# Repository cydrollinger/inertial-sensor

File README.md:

<a href="https://elec-real.com/case-studies/9-axis-inertial-data-logger/"></img></a>

>Electronic Realization L.L.C.								   
>Design: 9 axis inertial sensor with bluetooth communication		   
>Engineer: Cy Drollinger								   
>Date: 2/19												           
>Email: cy@elec-real.com
>Website: https://elec-real.com								   
>Address: 2023 Stadium Dr Suite 2B #210 Bozeman, MT 59715				   
>Phone: 406-539-8117	

**NOTE:**
 This design has been tested and functions as specified. The design is provided gratis, so, please 
 think critically while utilizing and or redesigning. Open electronic circuitry can be dangerous due 
 to easily shorting circuits which can generate immediate and intense heat resulting in fire. Conversation is
 welcome to improve this design and repository, but, be advised ER is a professional design house and
 monetary compensation is required for additional work toward this design enabling your success.			   

**PURPOSE:**
This electronic system is capable of sampling inertial data from the mpu9250 at 1 kHz and storing to 
a uSD card for GB storage, fatfs. The design files were created with Eagle Cadsoft v7.7 as a 
two layer board. Free Eagle version would be capable of viewing, and editing these files for redesign. 

>**File Arcitecture with a terse description**

* FOLDERS:
	* docs		: datasheets charging IC and battery holder
	* hardware	: eagle cadsoft(v7.7) hardware design files 	
		* eagleup		: 3D files 
		* library		: eagle part files 
		* manufacturing	: files required to produce the design
			* bom	: files created to order the parts
					* batteryCharger.txt	: 
					* batteryv1.1.csv	: digikey order
					* hundredUnits.txt	
			* gerber	: files generated to manufacture the board
			* <a href="https://oshpark.com/shared_projects/Yydb06ED"></img></a>
	* firmware
	* software

	* readme.md	: this file

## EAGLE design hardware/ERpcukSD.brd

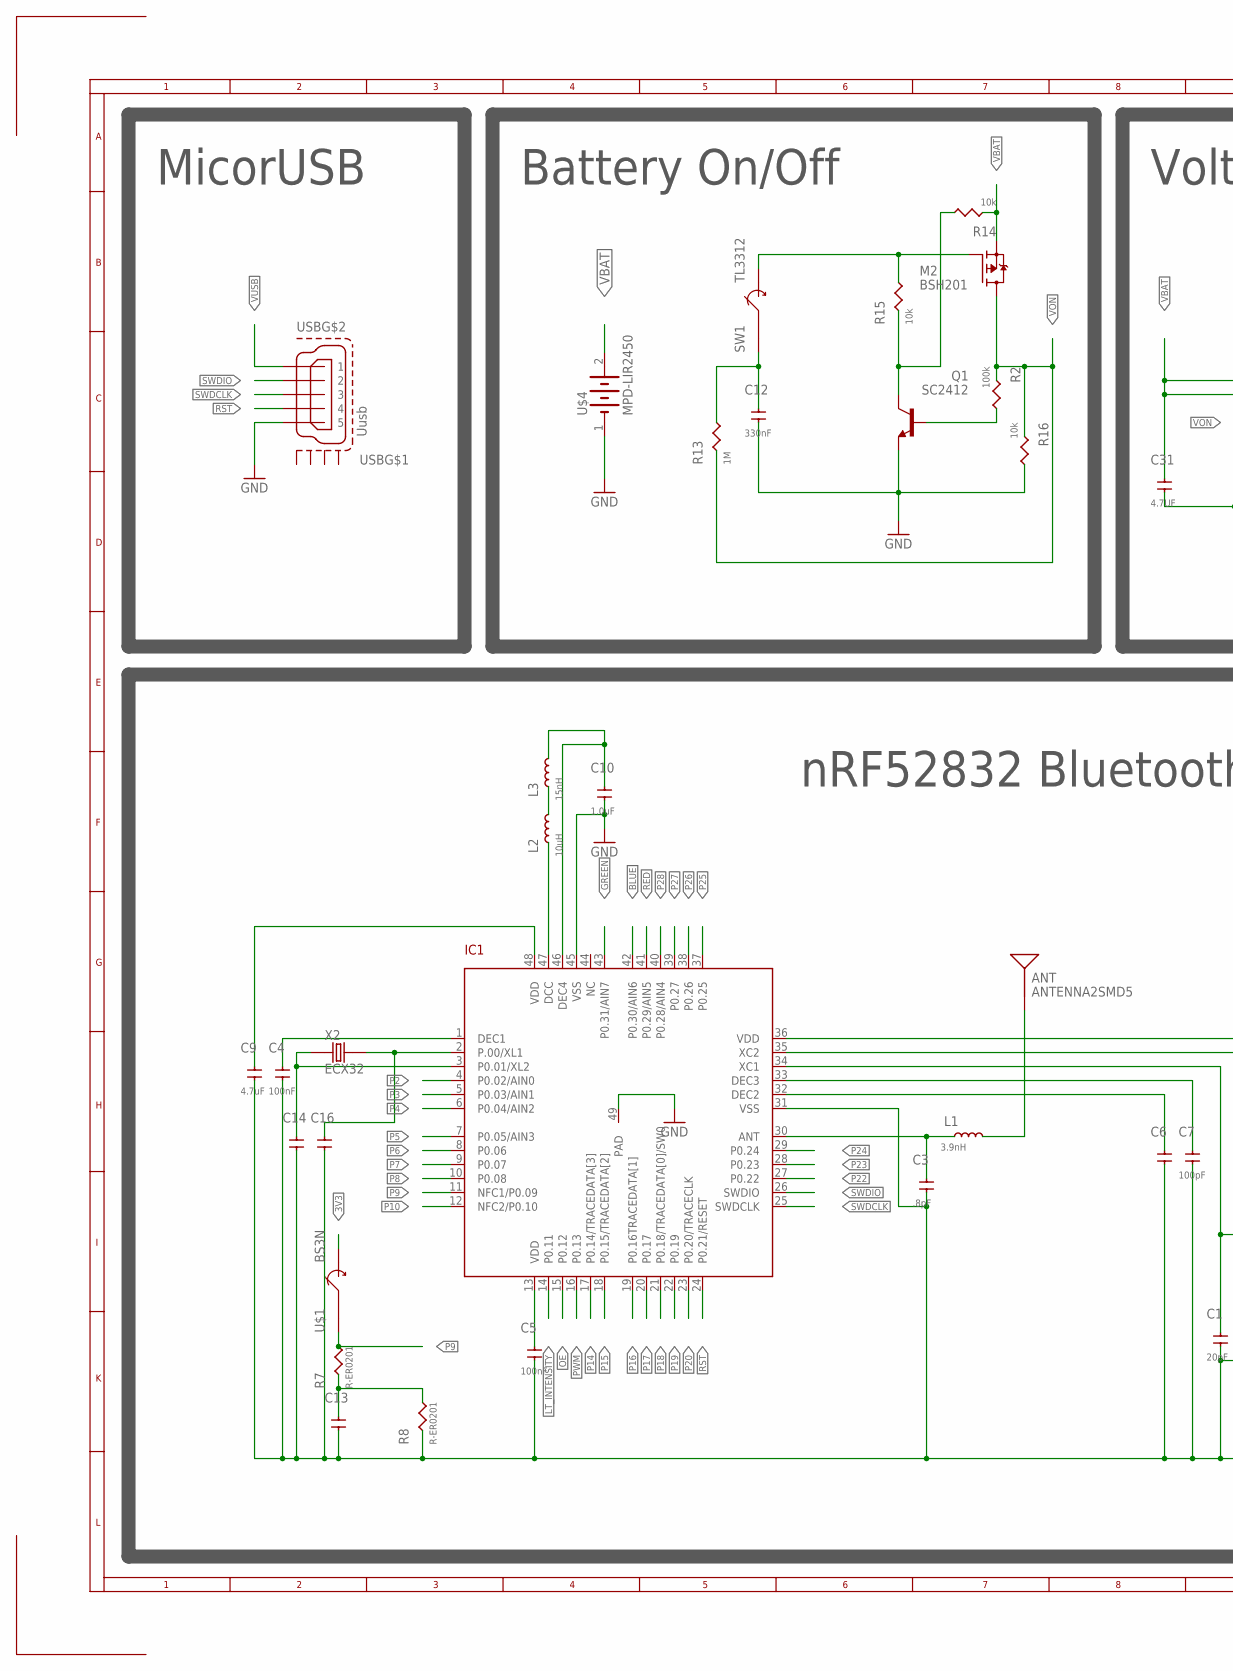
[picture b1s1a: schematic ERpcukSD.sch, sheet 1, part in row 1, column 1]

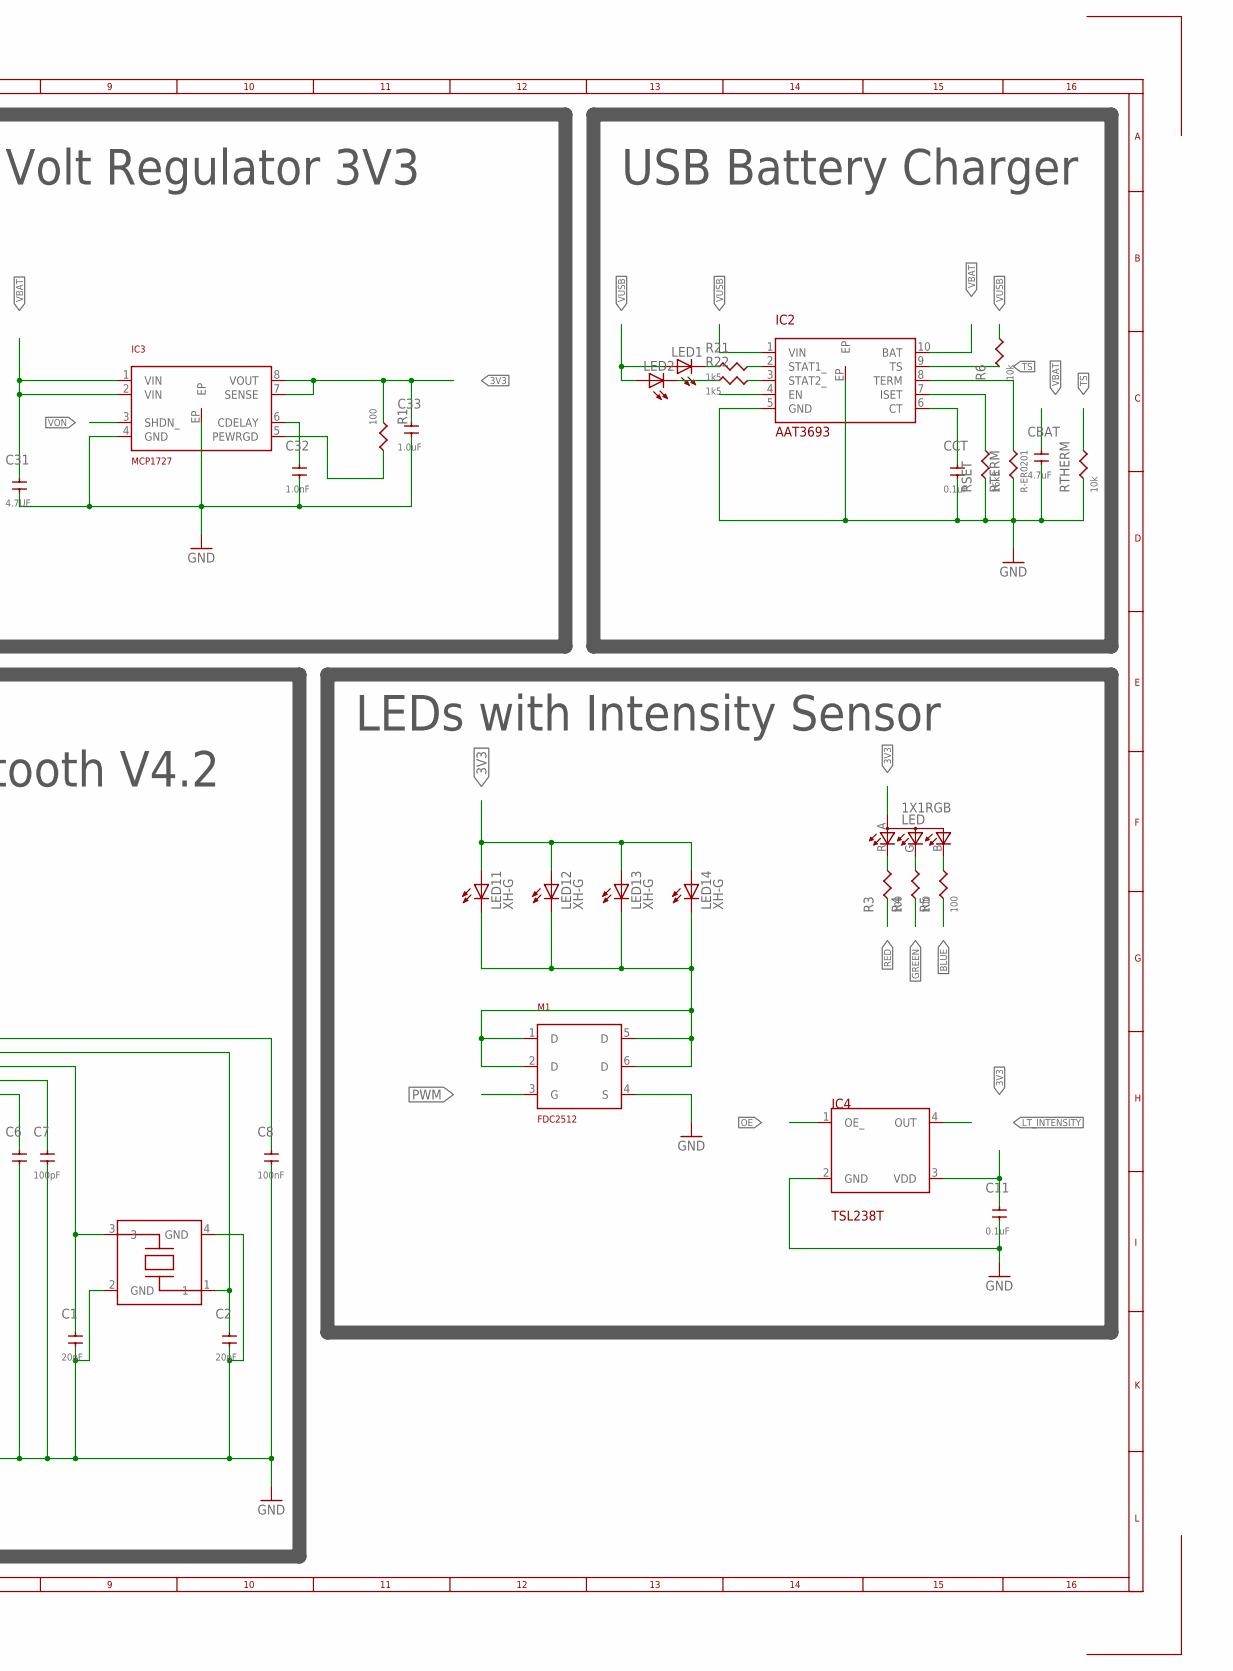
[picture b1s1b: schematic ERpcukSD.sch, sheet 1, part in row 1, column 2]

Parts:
ANT: ANTENNA2SMD5; ANTENNA-CHIP5
C1, C2: 20pF; C0201
C3: .8pF; C0201
C4, C5, C8: 100nF; C0201
C6, C13, C14, C16: C-ER201; C0201
C7: 100pF; C0201
C9: 4.7uF; C0402
C10, C33: 1.0uF; C0201
C11: 0.1uF; C0201
C12: 330nF; C0201
C31: 4.7UF; C0402
C32: 1.0nF; C0201
CBAT: 4.7uF; C0402
CCT: 0.1uF; C0201
IC1: NRF52832; QFN48
IC2: AAT3693
IC3: MCP1727; DFN8-3X3
IC4: TSL238T; T4
L1: 3.9nH; C0201
L2: 10uH; R0603
L3: 15nH; C0201
LED: 1X1RGB; 1X1
LED1, LED2: LEDCHIP-LED0603; CHIP-LED0603
LED11, LED12, LED13, LED14: XH-G
M1: FDC2512; SSOT6
M2: BSH201; SOT23
Q1: SC2412; SC59-BEC
R1, R3, R4, R5: 100; R0201
R2: 100k; R0201
R6, R14, R15, R16: 10k; R0201
R7, R8: R-ER0201; R0201
R13: 1M; R0201
R21, R22: 1k5; R0201
RSET: 16k5; R0201
RTERM: R-ER0201; R0201
RTHERM: 10k; R0201
SW1: TL3312; DIGIKEY EG4620CT-ND
U$1: BS3N
U$4: MPD-LIR2450; LIR2450
USB: Uusb; ZX62R-B-5P
X1: FA-128
X2: ECX32; ECX39

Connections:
3V3: C5.2, C8.2, C9.2, C11.2, C33.2, IC1.13 (VDD), IC1.36 (VDD), IC1.48 (VDD), IC3.7 (SENSE), IC3.8 (VOUT), IC4.3 (VDD), LED.A (A2), LED11.2 (A), LED12.2 (A), LED13.2 (A), LED14.2 (A), R1.1, U$1.2; also elsewhere on the board
BLUE: IC1.42 (P0.30/AIN6), R5.1
GND: C1.1, C2.1, C3.1, C4.1, C5.1, C6.1, C7.1, C8.1, C9.1, C10.1, C11.1, C12.1, C13.1, C14.1, C16.1, C31.1, C32.1, C33.1, CBAT.1, CCT.1, IC1.31 (VSS), IC1.45 (VSS), IC1.49 (PAD), IC2.5 (GND), IC2.EP, IC3.4 (GND), IC3.EP, IC4.2 (GND), M1.4 (S), Q1.E, R8.1, R16.2, RSET.1, RTERM.1, RTHERM.1, U$4.1 (-), USB.1 (5), X1.2 (GND), X1.4 (GND); also elsewhere on the board
GREEN: IC1.43 (P0.31/AIN7), R4.1
LT_INTENSITY: IC1.14 (P0.11), IC4.4 (OUT)
unnamed: LED11.1 (C), LED12.1 (C), LED13.1 (C), LED14.1 (C), M1.1 (D), M1.2 (D), M1.5 (D), M1.6 (D)
unnamed: Q1.B, R2.2
unnamed: C3.2, IC1.30 (ANT), L1.1
unnamed: C6.2, IC1.32 (DEC2)
unnamed: ANT.FEED, L1.2
unnamed: C7.2, IC1.33 (DEC3)
unnamed: C1.2, IC1.34 (XC1), X1.3
unnamed: C2.2, IC1.35 (XC2), X1.1
unnamed: Q1.C, R14.2, R15.1
unnamed: IC1.47 (DCC), L2.1
unnamed: L2.2, L3.1
unnamed: C10.2, IC1.46 (DEC4), L3.2
unnamed: C12.2, R13.2, SW1.1
unnamed: LED.B (CGREEN), R5.2
unnamed: CCT.2, IC2.6 (CT)
unnamed: IC2.7 (ISET), RSET.2
unnamed: IC2.8 (TERM), RTERM.2
unnamed: IC2.3 (STAT2_), R22.2
unnamed: IC2.2 (STAT1_), R21.2
unnamed: LED1.C, R21.1
unnamed: LED2.C, R22.1
unnamed: LED.G (CBLUE), R4.2
unnamed: IC3.5 (PEWRGD), R1.2
unnamed: LED.R (CRED), R3.2
unnamed: C32.2, IC3.6 (CDELAY)
unnamed: M2.1 (G), R15.2, SW1.3 (2)
unnamed: C16.2, IC1.2 (P.00/XL1), X2.P$2 (2)
unnamed: C14.2, IC1.3 (P0.01/XL2), X2.P$1 (1)
unnamed: C4.2, IC1.1 (DEC1)
unnamed: C13.2, R7.1, R8.2
OE: IC1.15 (P0.12), IC4.1 (OE_)
P2: IC1.4 (P0.02/AIN0); also elsewhere on the board
P3: IC1.5 (P0.03/AIN1); also elsewhere on the board
P4: IC1.6 (P0.04/AIN2); also elsewhere on the board
P5: IC1.7 (P0.05/AIN3); also elsewhere on the board
P6: IC1.8 (P0.06); also elsewhere on the board
P7: IC1.9 (P0.07); also elsewhere on the board
P8: IC1.10 (P0.08); also elsewhere on the board
P9: IC1.11 (NFC1/P0.09), R7.2, U$1.1
P10: IC1.12 (NFC2/P0.10); also elsewhere on the board
P14: IC1.17 (P0.14/TRACEDATA[3]); also elsewhere on the board
P15: IC1.18 (P0.15/TRACEDATA[2]); also elsewhere on the board
P16: IC1.19 (P0.16TRACEDATA[1]); also elsewhere on the board
P17: IC1.20 (P0.17); also elsewhere on the board
P18: IC1.21 (P0.18/TRACEDATA[0]/SW0); also elsewhere on the board
P19: IC1.22 (P0.19); also elsewhere on the board
P20: IC1.23 (P0.20/TRACECLK); also elsewhere on the board
P22: IC1.27 (P0.22); also elsewhere on the board
P23: IC1.28 (P0.23)
P24: IC1.29 (P0.24)
P25: IC1.37 (P0.25)
P26: IC1.38 (P0.26)
P27: IC1.39 (P0.27)
P28: IC1.40 (P0.28/AIN4)
PWM: IC1.16 (P0.13), M1.3 (G)
RED: IC1.41 (P0.29/AIN5), R3.1
RST: IC1.24 (P0.21/RESET), USB.2 (4)
SWDCLK: IC1.25 (SWDCLK), USB.3
SWDIO: IC1.26 (SWDIO), USB.4 (2)
TS: IC2.9 (TS), R6.1, RTHERM.2
VBAT: C31.2, CBAT.2, IC2.10 (BAT), IC3.1 (VIN), IC3.2 (VIN), M2.2 (S), R14.1, U$4.2 (+)
VON: IC3.3 (SHDN_), M2.3 (D), R2.1, R13.1, R16.1
VUSB: IC2.1 (VIN), IC2.4 (EN), LED1.A, LED2.A, R6.2, USB.5 (1)

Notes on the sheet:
nRF52832 Bluetooth V4.2
MicorUSB
Battery On/Off
Volt Regulator 3V3
USB Battery Charger
LEDs with Intensity Sensor

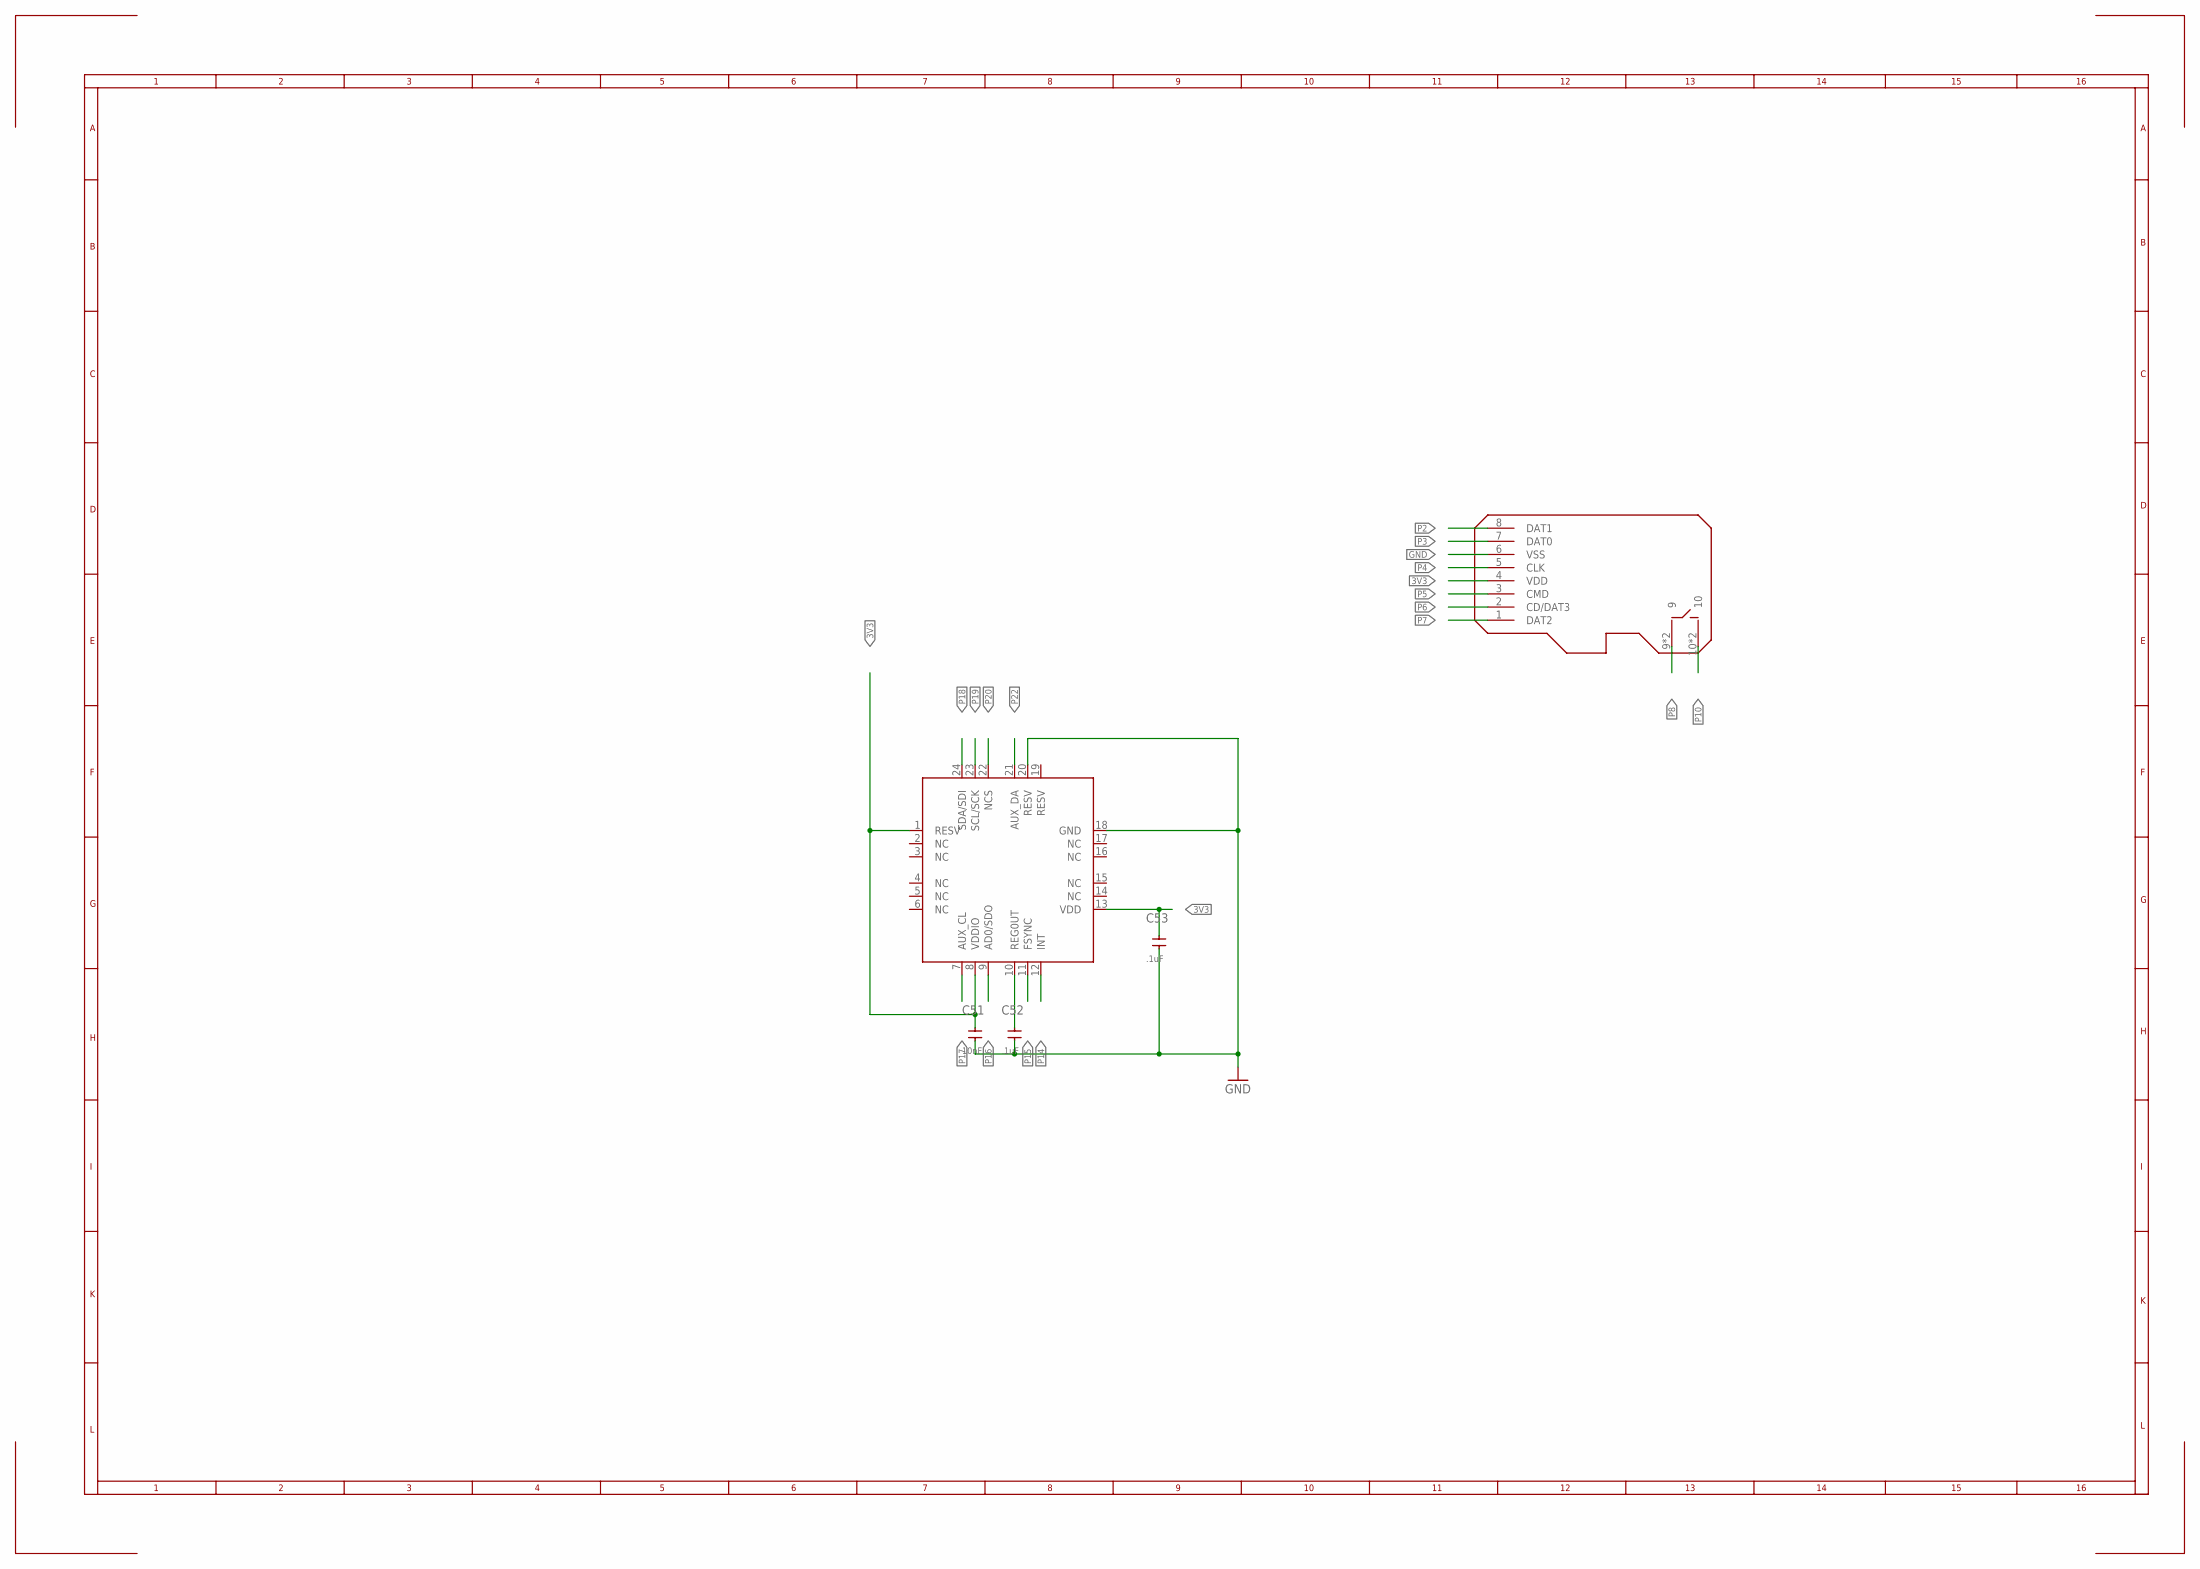
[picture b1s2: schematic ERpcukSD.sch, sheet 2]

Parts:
C51: 10nF; C0201
C52, C53: .1uF; C0201
IC5: MPU9250; 3X3_24_QFN_CORRECTED
U$2: MICROSD

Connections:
3V3: C51.2, C53.2, IC5.1 (RESV), IC5.8 (VDDIO), IC5.13 (VDD), U$2.4 (VDD); also elsewhere on the board
GND: C51.1, C52.1, C53.1, IC5.18 (GND), IC5.20 (RESV), U$2.6 (VSS); also elsewhere on the board
unnamed: C52.2, IC5.10 (REG0UT)
P2: U$2.8 (DAT1); also elsewhere on the board
P3: U$2.7 (DAT0); also elsewhere on the board
P4: U$2.5 (CLK); also elsewhere on the board
P5: U$2.3 (CMD); also elsewhere on the board
P6: U$2.2 (CD/DAT3); also elsewhere on the board
P7: U$2.1 (DAT2); also elsewhere on the board
P8: U$2.9, U$2.9@1 (9); also elsewhere on the board
P10: U$2.10, U$2.10@1 (10); also elsewhere on the board
P14: IC5.12 (INT); also elsewhere on the board
P15: IC5.11 (FSYNC); also elsewhere on the board
P16: IC5.9 (AD0/SDO); also elsewhere on the board
P17: IC5.7 (AUX_CL); also elsewhere on the board
P18: IC5.24 (SDA/SDI); also elsewhere on the board
P19: IC5.23 (SCL/SCK); also elsewhere on the board
P20: IC5.22 (NCS); also elsewhere on the board
P22: IC5.21 (AUX_DA); also elsewhere on the board

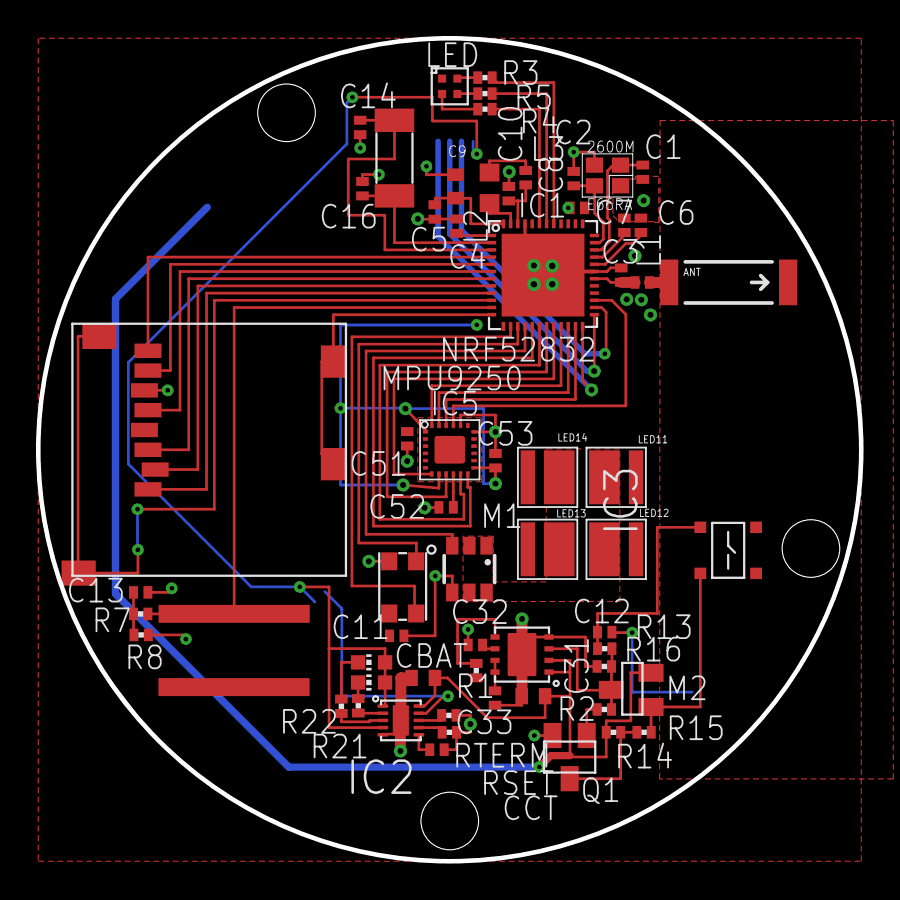
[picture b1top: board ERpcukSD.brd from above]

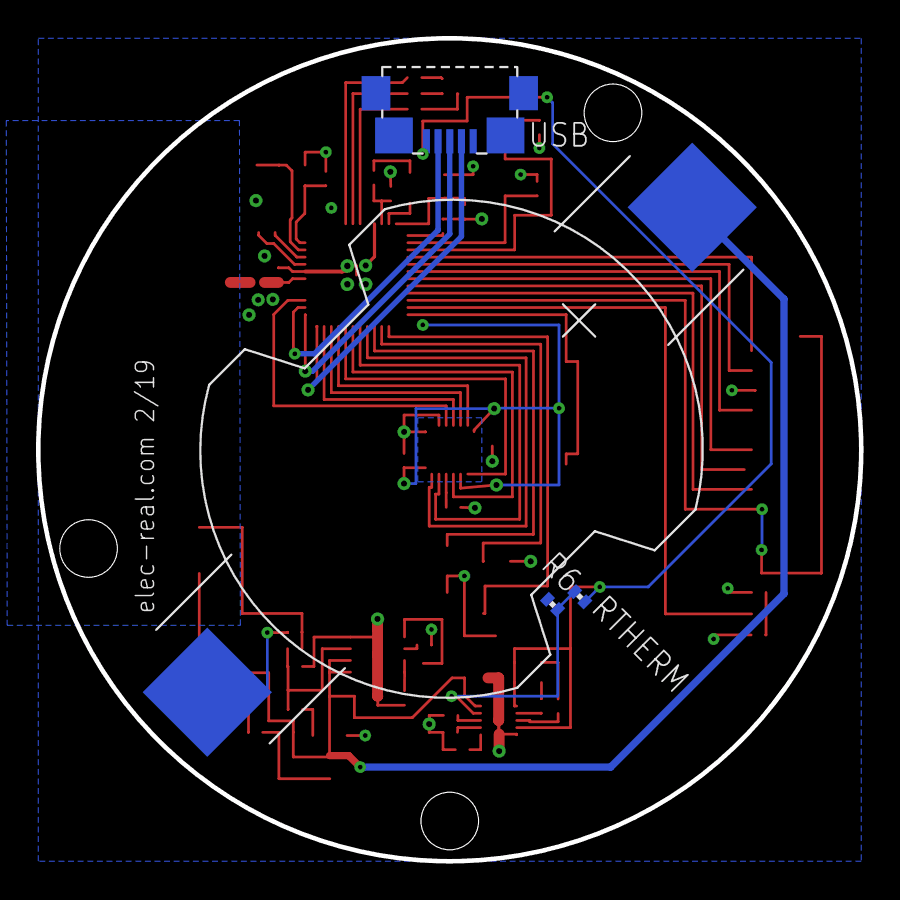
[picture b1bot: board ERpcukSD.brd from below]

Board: 2 copper layers, 45.7 x 45.7 mm, 66 parts (4 on the bottom side), 63 nets.

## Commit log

2019-04-18 first commit of files 4/18/19
2019-04-26 first commit 4/26/19
2019-04-27 first commit 4/27/19
2019-04-30 first commit 4/30/19
